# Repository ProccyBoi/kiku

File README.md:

# kiku

kiku is an open-source portable audio player built around an STM32H523 microcontroller. The project combines Bluetooth audio, local microSD playback, FM radio, a colour display, headphone and speaker outputs, battery management, and a custom mechanical enclosure in one hardware/firmware repository.

> **Project status:** this repository is a public engineering snapshot, not a production-approved hardware release. The firmware software gate passes on the checked-in source, but physical product qualification is still in progress. In particular, the Rev-A USB-C/power-path issue and the remaining hardware soak/validation items in [`Firmware/RELEASE_CHECKLIST.md`](Firmware/RELEASE_CHECKLIST.md) must be resolved before treating the design as production-ready. Files under `Production/` are therefore prototype/reference manufacturing outputs, not a production release.

## Features

- Bluetooth A2DP sink with AVRCP transport control and metadata through a Microchip BM83
- WAV and MP3 playback from a 4-bit SDMMC microSD card
- FM tuning, seek and RDS using the Silicon Labs SI4705-D60
- TLV320AIC3104 headphone/codec path and MAX98357A internal-speaker amplifier
- automatic headphone/speaker routing
- 2.0-inch 240 x 320 ST7789 display, rotary encoder and push-button controls
- BQ25895 charging/power-path control and MAX17048 battery state-of-charge monitoring
- FreeRTOS-based STM32H523 firmware with host tests, release/debug builds, watchdogs and diagnostics
- project-owned enclosure CAD, printable parts and mechanical packaging tools

## Hardware

The KiCad project in the repository root is the electrical hardware source of truth. The current board uses:

| Function | Device |
| --- | --- |
| Application MCU | STM32H523VET6 |
| Bluetooth audio | Microchip BM83, A2DP sink |
| Audio codec / headphones | TI TLV320AIC3104 |
| Speaker amplifier | Analog Devices MAX98357A |
| FM receiver | Silicon Labs SI4705-D60 |
| Charger / power path | TI BQ25895 |
| Fuel gauge | Analog Devices MAX17048 |
| Display | HS20HS072RX, ST7789, 240 x 320 |
| Storage | 4-bit SDMMC microSD |

The board is programmed and debugged through **SWD**. On this hardware revision, USB-C D+/D- are used by the BQ25895 input-detection circuitry and are **not routed to STM32 PA11/PA12**, so USB DFU/CDC is not available.

The historical `Walkman - Blobject.*` KiCad/manufacturing filenames are retained in this snapshot to avoid breaking project references and release tooling; the public project name is **kiku**.

## Firmware

Firmware is under [`Firmware/`](Firmware/README.md). It implements Bluetooth, local-file and FM source handling; audio routing; display and controls; battery/charger monitoring; persistent settings; watchdog/fault handling; and bring-up diagnostics.

Initialise the pinned submodules and run the host/build checks from the repository root:

```text
git submodule update --init --recursive
python Firmware/tools/test_host.py
python Firmware/tools/build.py --clean
```

For a software release candidate, run:

```text
python Firmware/tools/release_check.py --require-clean
```

The firmware build outputs `kiku.elf`, `kiku.bin`, `kiku.hex` and `kiku.map` under `Firmware/build/`. See [`Firmware/README.md`](Firmware/README.md) for the BM83 configuration contract, programming steps, controls and bring-up details.

## Mechanical design

[`Mechanical/`](Mechanical/README.md) contains the enclosure source, public STEP/STL outputs, review material and packaging scripts.

The project intentionally does **not** redistribute component 3D models whose upstream redistribution terms are unclear, nor generated populated/reference assemblies that embed those models. Public mechanical packages use project-owned geometry and recorded QA metadata. Exact component-level fit checking remains a local workflow after obtaining the required manufacturer/KiCad models under their original terms.

See [`Mechanical/REFERENCE_GEOMETRY.md`](Mechanical/REFERENCE_GEOMETRY.md) for the complete provenance and reproducibility workflow.

## Repository layout

```text
Firmware/                       STM32 firmware, tests and build/release tooling
Mechanical/                     enclosure CAD, exports, QA and packaging tools
Production/                     prototype/reference PCB manufacturing outputs
3dmodels/README.md              policy for locally obtained component models
Walkman - Blobject.kicad_*      KiCad project sources
Print.pdf                       generated PCB print output
Print Schematic.pdf             generated schematic print output
.github/workflows/firmware.yml  firmware CI
```

## Public-source scope

This repository publishes project-authored hardware, firmware and mechanical sources while deliberately excluding material that should remain with its upstream publisher. Excluded material includes third-party BM83 firmware/configuration tools and command-set documents, generated radio images, cached supplier pages, vendor datasheet copies, provenance-unclear component 3D models, and fit-check assemblies that serialise those models.

Third-party source code that is present in the tree or pulled as a submodule remains under its own upstream copyright and licence notices. The project licence does not replace those terms.

## Validation

The public snapshot is checked with:

- native firmware regression tests plus clean release/debug ARM builds;
- `Firmware/tools/release_check.py --require-clean`;
- stripped-checkout P0/P1 mechanical package builds that exclude third-party reference geometry;
- Git history, integrity, privacy and credential scans before publication.

Passing these source/software checks does not replace the physical hardware, RF, charging, mechanical, regulatory or long-duration soak tests listed in [`Firmware/RELEASE_CHECKLIST.md`](Firmware/RELEASE_CHECKLIST.md).

## Licence

kiku is a mixed-licence project:

- project-authored hardware, electronics and mechanical design material is licensed under **CERN-OHL-P-2.0**;
- project-authored firmware, tools, scripts and CI code is licensed under the **MIT License**;
- files or portions carrying their own third-party copyright/licence notices remain under those upstream terms.

The exact scope map and full licence texts are in [`LICENSE`](LICENSE) and [`LICENSES/`](LICENSES/).

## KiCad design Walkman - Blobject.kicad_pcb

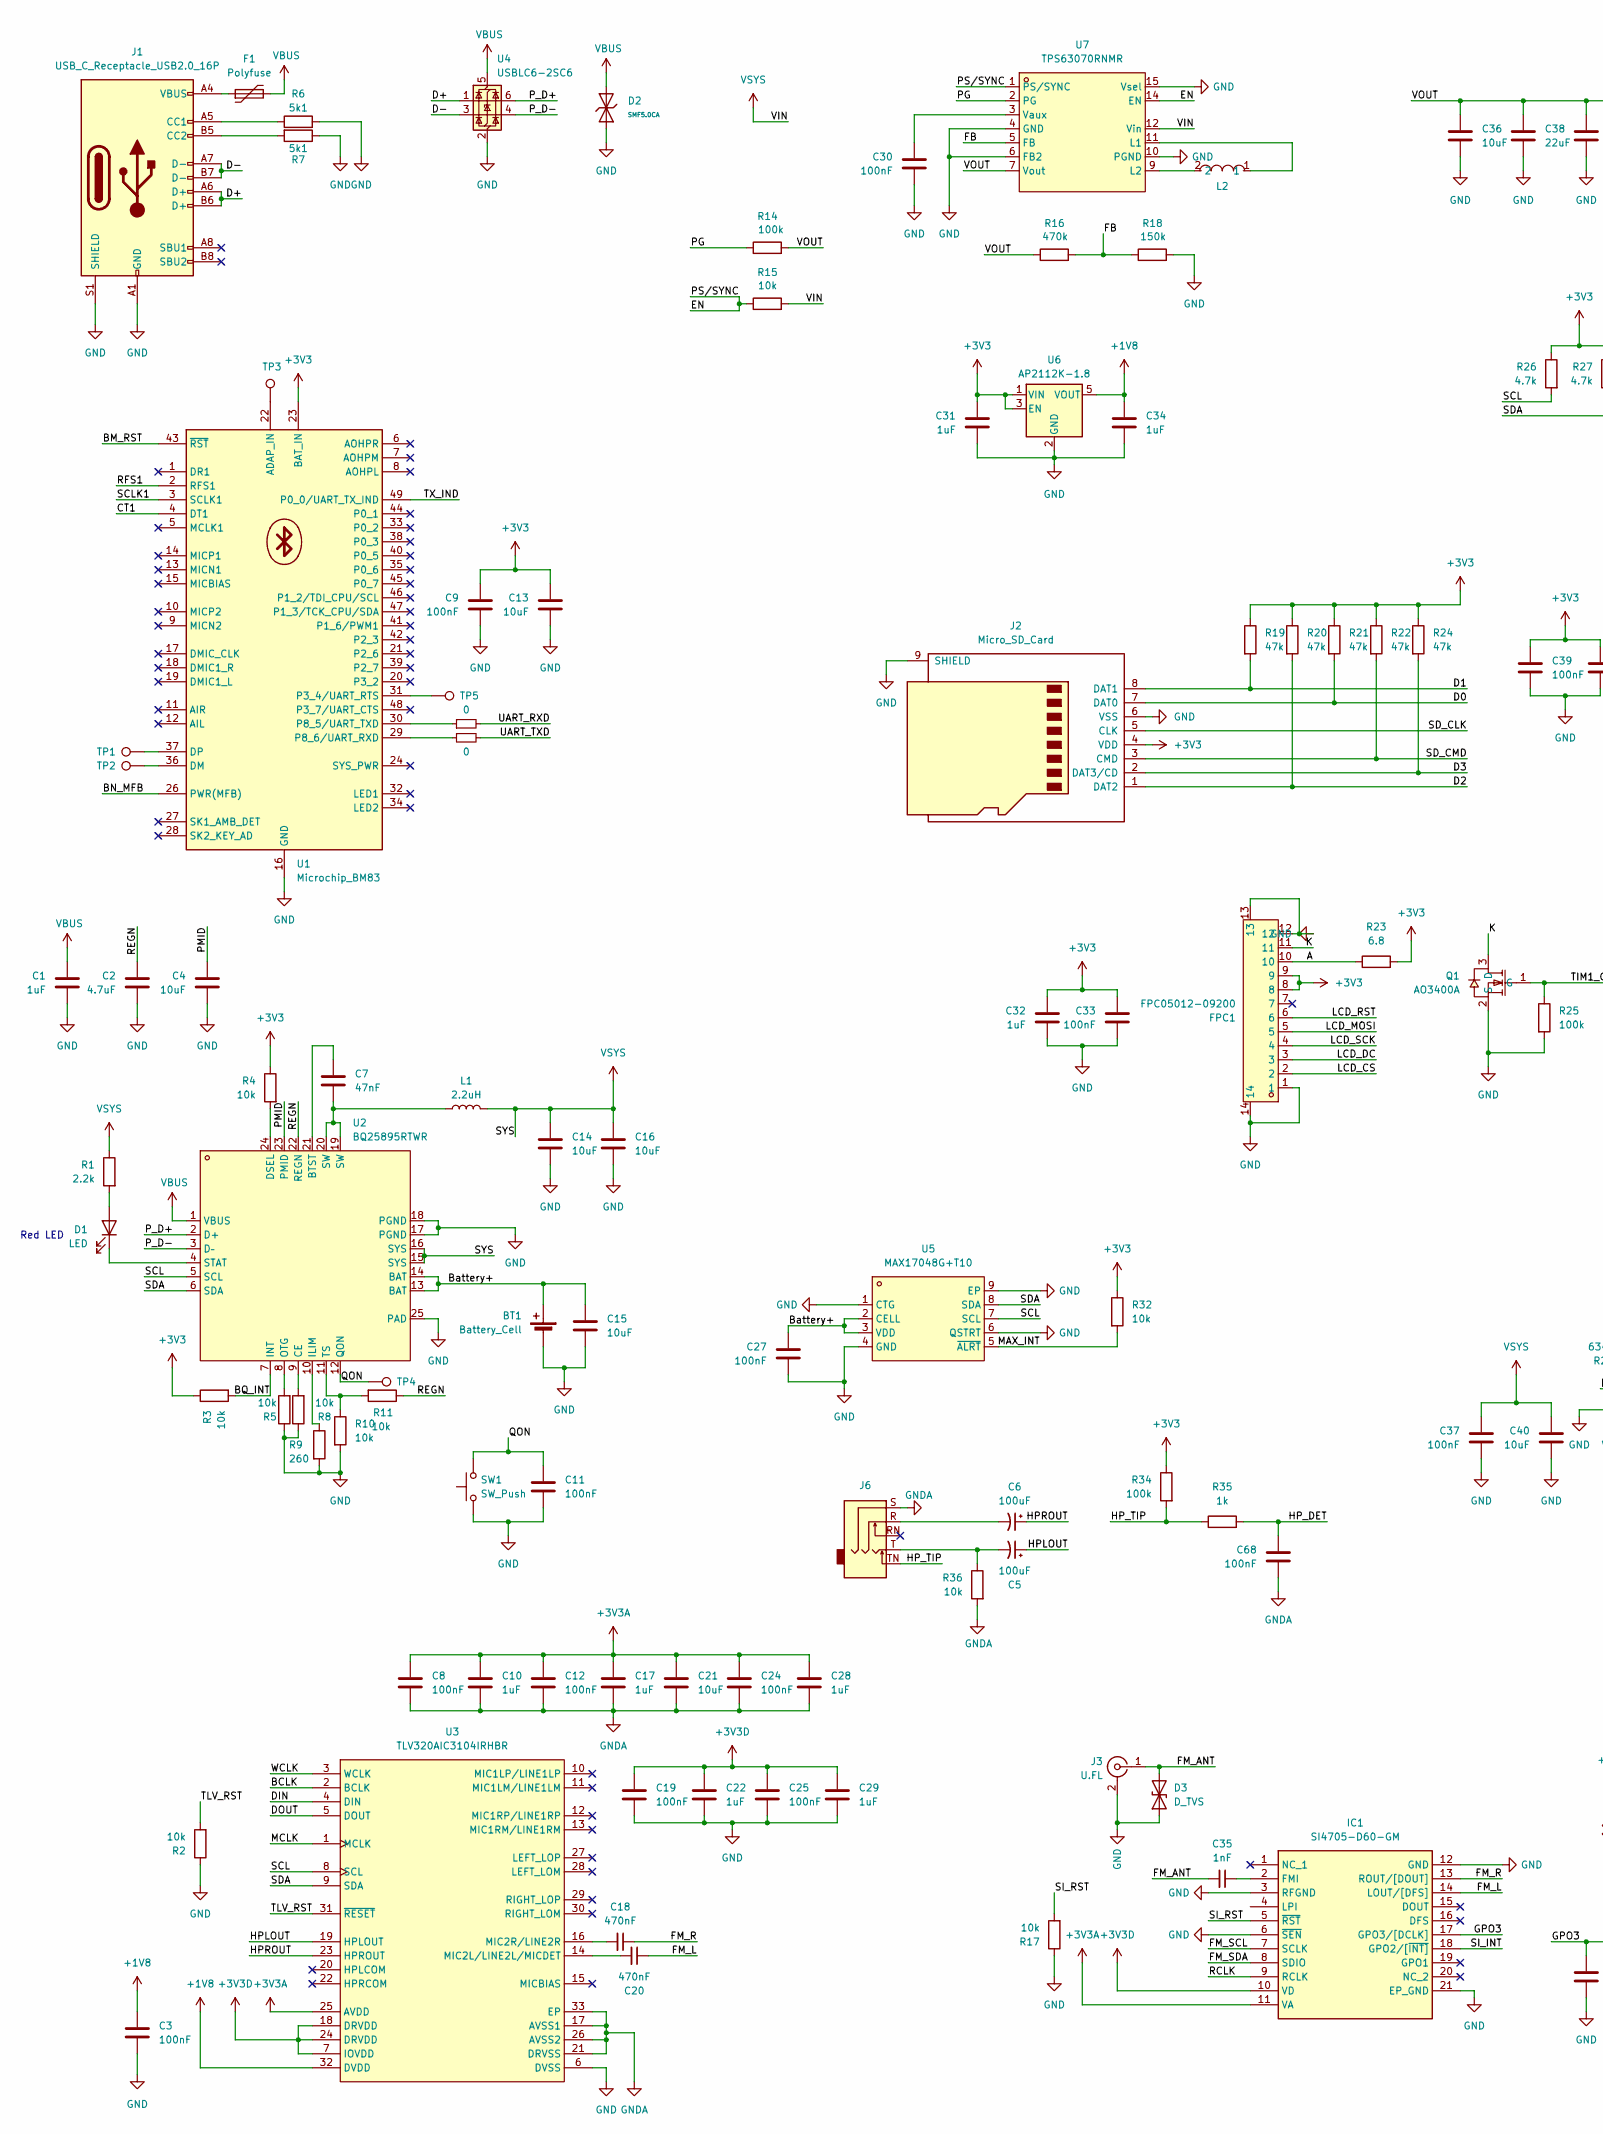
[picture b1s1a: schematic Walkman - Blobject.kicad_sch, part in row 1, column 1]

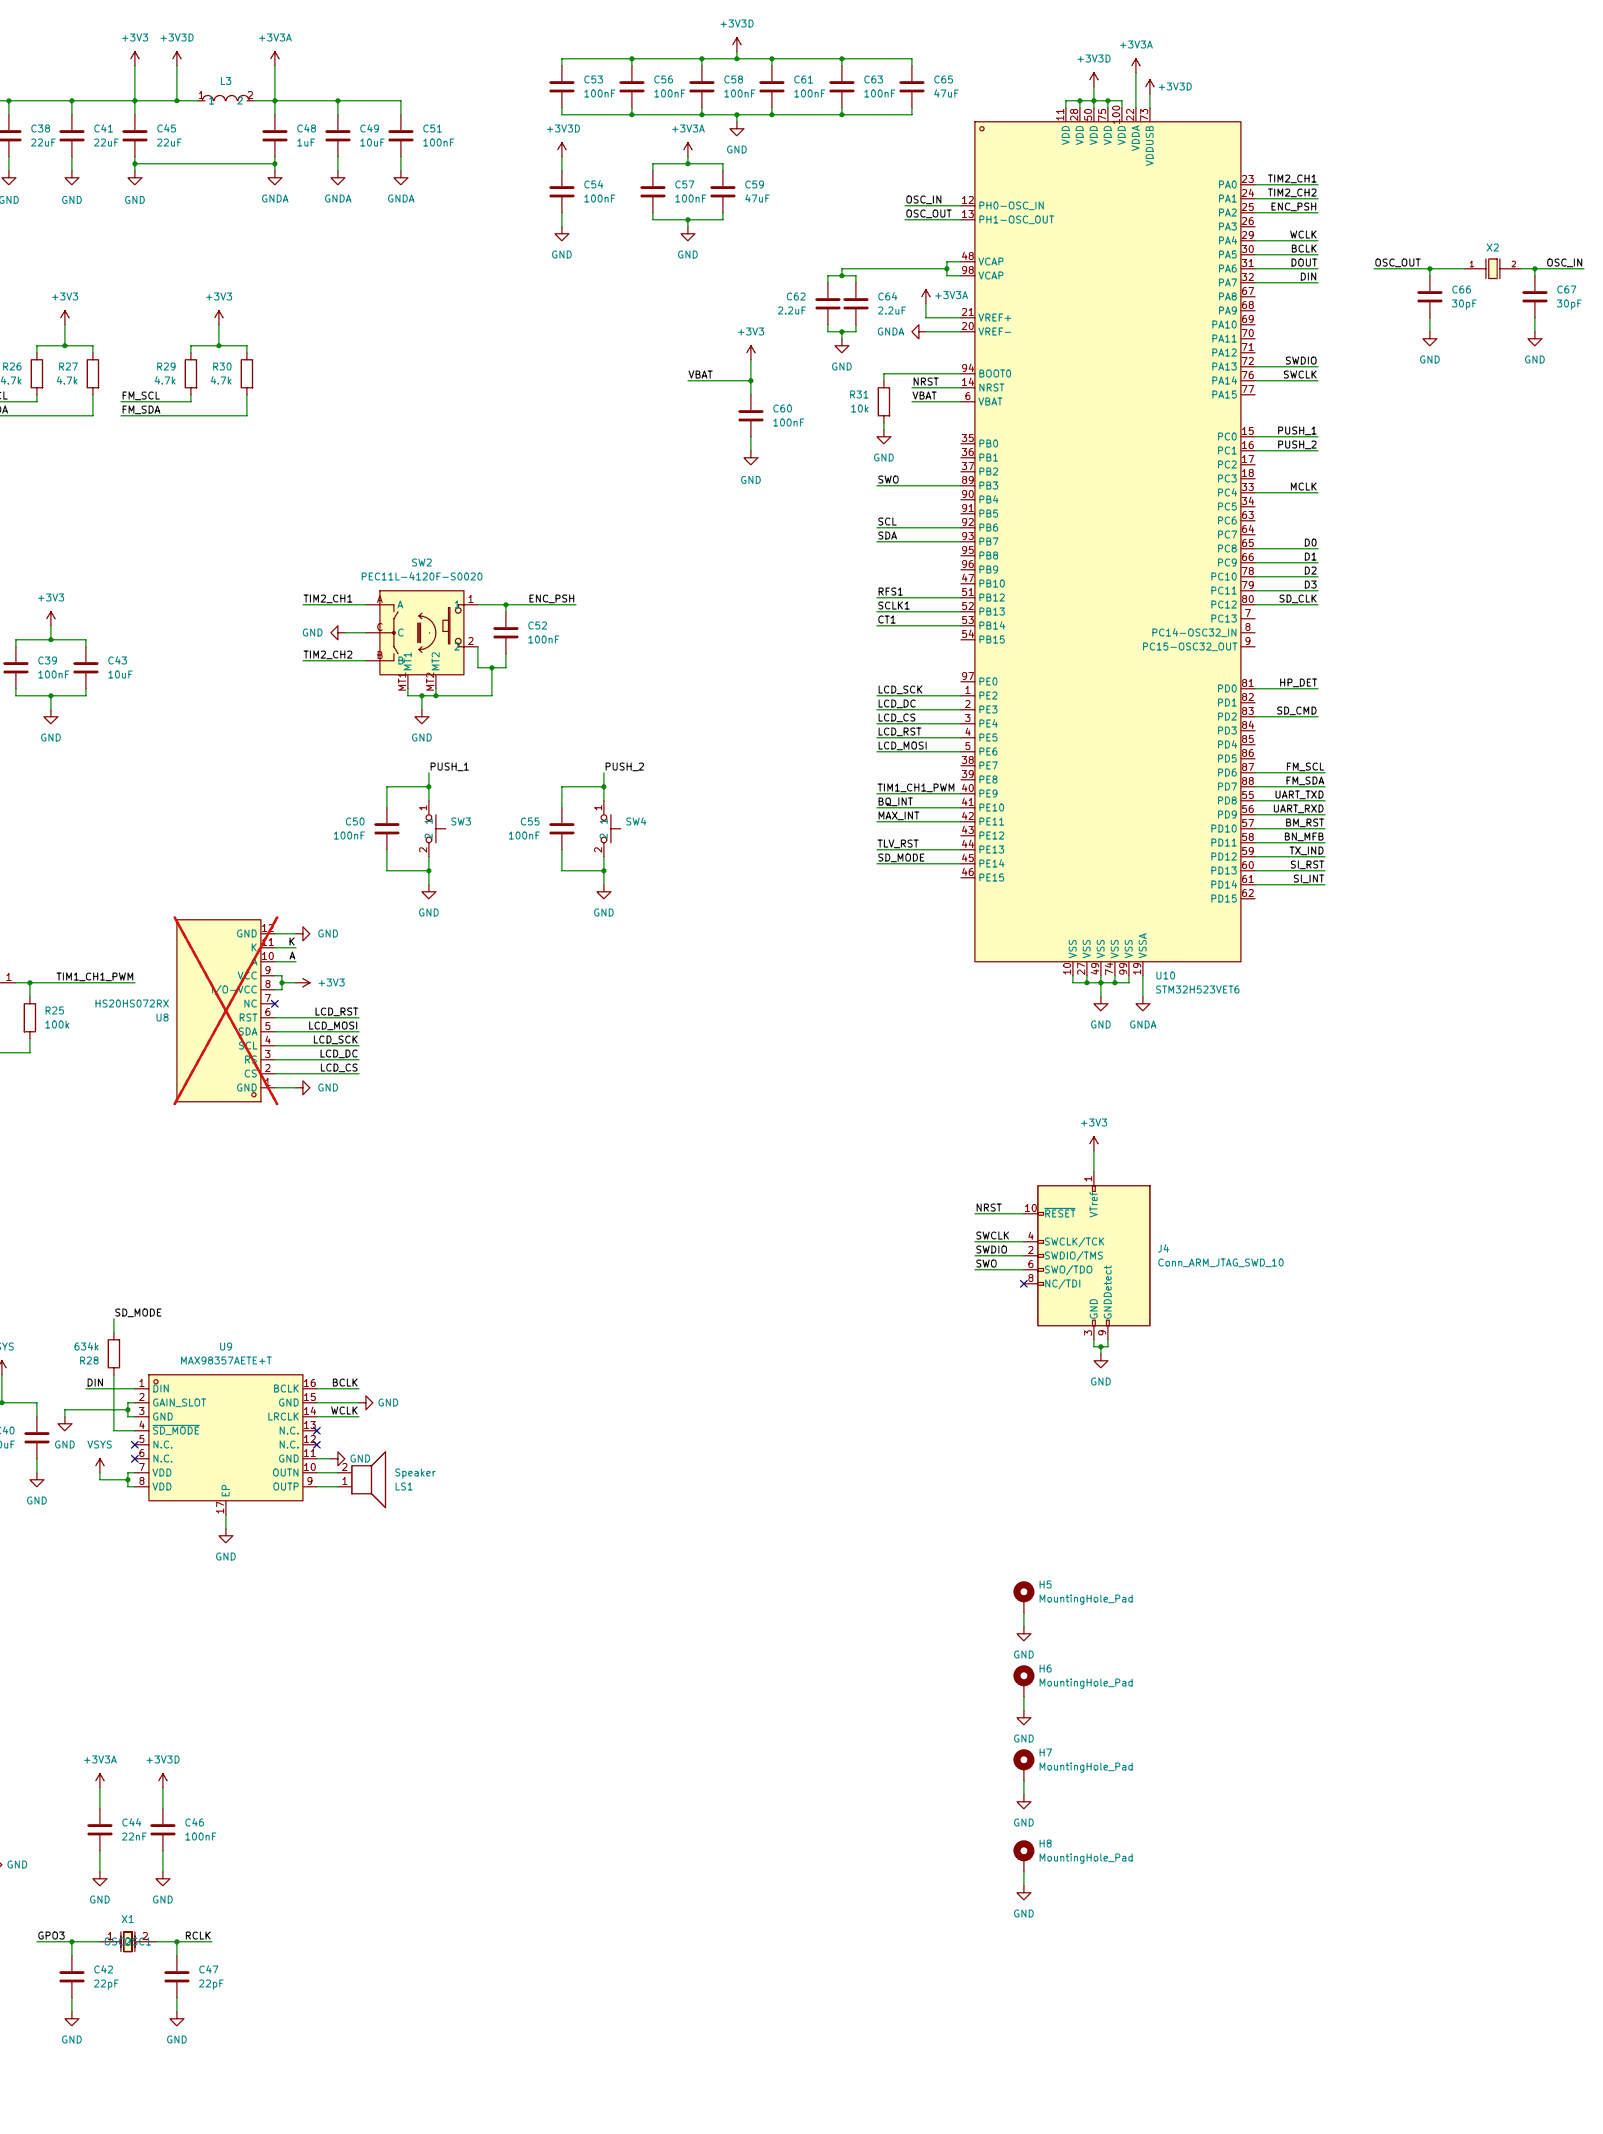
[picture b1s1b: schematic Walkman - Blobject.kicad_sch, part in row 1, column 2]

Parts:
BT1: Battery_Cell; JST_PH_B2B-PH-K_1x02_P2.00mm_Vertical
C1, C10, C17, C22, C28, C29, C31, C32, C34, C48: 1uF; C_0603_1608Metric
C2: 4.7uF; C_0603_1608Metric
C3, C8, C9, C11, C12, C19, C24, C25, C27, C30, C33, C37, C39, C46, C50, C51, C52, C53, C54, C55, C56, C57, C58, C60, C61, C63, C68: 100nF; C_0603_1608Metric
C4, C13, C14, C15, C16, C21, C36, C40, C43, C49: 10uF; C_0603_1608Metric
C5, C6: 100uF; CP_Elec_5x5.4
C7: 47nF; C_0603_1608Metric
C18, C20: 470nF; C_0603_1608Metric
C35: 1nF; C_0201_0603Metric
C38, C41, C45: 22uF; C_0603_1608Metric
C42, C47: 22pF; C_0603_1608Metric
C44: 22nF; C_0603_1608Metric
C59, C65: 47uF; C_0603_1608Metric
C62, C64: 2.2uF; C_0603_1608Metric
C66, C67: 30pF; C_0603_1608Metric
D1: LED; LED_0603_1608Metric
D2: SMF5.0CA; D_SOD-123FL; Part SMF5.0CA; LCSC C19077498
D3: D_TVS; D_0201_0603Metric; LCSC C672369
F1: Polyfuse; Fuse_1206_3216Metric; LCSC C883127
FPC1: FPC05012-09200; FPC-SMD_FPC05012-09200; MPN FPC05012-09200; LCSC Part C479750
H5, H6, H7, H8: MountingHole_Pad; MountingHole_2.2mm_M2_Pad_Via
IC1: SI4705-D60-GM; SI4705D60GM; Manufacturer_Part_Number SI4705-D60-GM; Mouser Part Number N/A
J1: USB_C_Receptacle_USB2.0_16P; USB_C_Receptacle_HRO_TYPE-C-31-M-12; LCSC C2765186
J2: Micro_SD_Card; microSD_HC_Hirose_DM3AT-SF-PEJM5
J3: U.FL; IPEX-SMD_BWIPX-1-001E; LCSC C5137195
J4: Conn_ARM_JTAG_SWD_10; PinHeader_2x05_P1.27mm_Vertical
J6: AudioJack3_SwitchTR; Jack_3.5mm_CUI_SJ1-3525N_Horizontal
L1: 2.2uH; IND-SMD_L5.0-W5.0_SWPA5040S
L2: XFL4020-152MEC; IND-SMD_L4.0-W4.0-A; MPN XFL4020-152MEC; LCSC Part C3033018
L3: MPZ2012S601AT000; L0805; MPN MPZ2012S601AT000; LCSC Part C21519
LS1: Speaker; Molex_PicoBlade_53398-0271_1x02-1MP_P1.25mm_Vertical
Q1: AO3400A; SOT-23-3_L2.9-W1.3-P1.90-LS2.4-BR; MPN AO3400A; LCSC Part C20917
R1: 2.2k; R_0603_1608Metric
R2, R3, R4, R5, R8, R10, R11, R15, R17, R31, R32, R36: 10k; R_0603_1608Metric
R6, R7: 5k1; R_0603_1608Metric; LCSC C27834
R9: 260; R_0603_1608Metric
R12, R13: 0; R_0603_1608Metric
R14, R25, R34: 100k; R_0603_1608Metric
R16: 470k; R_0603_1608Metric
R18: 150k; R_0603_1608Metric
R19, R20, R21, R22, R24: 47k; R_0603_1608Metric; LCSC C17673
R23: 6.8; R_0603_1608Metric; LCSC C17673
R26, R27, R29, R30: 4.7k; R_0603_1608Metric
R28: 634k; R_0603_1608Metric
R35: 1k; R_0603_1608Metric; LCSC C17673
SW1: SW_Push; SW-SMD_L3.9-W3.0-P4.45
SW2: PEC11L-4120F-S0020; SW-TH_PEC11R-4XXXF-SXXXX; MPN PEC11L-4120F-S0020; LCSC Part C20882995
SW3, SW4: SW_PUSH_12x12x12mm_4Pin_SMD; MPN 12x12x12mm 4-pin tactile pushbutton
TP1, TP2, TP3, TP4, TP5: TestPoint; TestPoint_Pad_D1.0mm
U1: Microchip_BM83
U2: BQ25895RTWR; QFN-24_L4.0-W4.0-P0.50-TL-EP2.7; MPN BQ25895RTWR; LCSC Part C80200
U3: TLV320AIC3104IRHBR; HVQFN-32_L5.0-W5.0-P0.50-TL-EP; MPN TLV320AIC3104IRHBR; LCSC Part C181753
U4: USBLC6-2SC6; SOT-23-6
U5: MAX17048G+T10; TDFN-8_L2.0-W2.0-P0.50-BL-EP1.2; MPN MAX17048G+T10; LCSC Part C2682616
U6: AP2112K-1.8; SOT-23-5
U7: TPS63070RNMR; VQFN-15_L3.0-W2.5-P0.50-BL; MPN TPS63070RNMR; LCSC Part C109322
U8: HS20HS072RX; OLED-SMD_HS20HS072RX; MPN HS20HS072RX; LCSC Part C5329582; not fitted
U9: MAX98357AETE+T; TQFN-16_L3.0-W3.0-P0.50-BL-EP1.5; MPN MAX98357AETE+T; LCSC Part C910544
U10: STM32H523VET6; LQFP-100_L14.0-W14.0-P0.50-LS16.0-BL; MPN STM32H523VET6; LCSC Part C27338462
X1: ABS07-32.768KHZ-T; OSC-SMD_2P-L3.2-W1.5; MPN ABS07-32.768KHZ-T; LCSC Part C130253
X2: X50328MSB2GI; CRYSTAL-SMD_L5.0-W3.2; Frequency Tolerance ±10ppm; Part X50328MSB2GI; LCSC C115962

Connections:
+1V8: C3.2, C34.2, U3.32 (DVDD), U6.5 (VOUT)
+3V3: C9.1, C13.1, C19.1, C22.1, C25.1, C29.1, C31.2, C32.1, C33.1, C36.1, C38.1, C39.1, C41.1, C43.1, C45.1, C46.1, C53.1, C54.1, C56.1, C58.1, C60.1, C61.1, C63.1, C65.1, FPC1.8, FPC1.9, IC1.10 (VD), J2.4 (VDD), J4.1 (VTref), L3.1, R3.1, R4.1, R14.2, R16.1, R19.1, R20.1, R21.1, R22.1, R23.2, R24.1, R26.1, R27.1, R29.1, R30.1, R32.1, R34.1, U1.23 (BAT_IN), U3.7 (IOVDD), U3.18 (DRVDD), U3.24 (DRVDD), U6.1 (VIN), U6.3 (EN), U7.7 (Vout), U8.8 (I/O-VCC), U8.9 (VCC), U10.6 (VBAT), U10.11 (VDD), U10.28 (VDD), U10.50 (VDD), U10.73 (VDDUSB), U10.75 (VDD), U10.100 (VDD)
+3V3A: C8.1, C10.1, C12.1, C17.1, C21.1, C24.1, C28.1, C44.1, C48.1, C49.1, C51.1, C57.1, C59.1, IC1.11 (VA), L3.2, U3.25 (AVDD), U10.21 (VREF+), U10.22 (VDDA)
/A: FPC1.10, R23.1, U8.10 (A)
/BCLK: U3.2 (BCLK), U9.16 (BCLK), U10.30 (PA5)
/BM_RST: U1.43 (~RST), U10.57 (PD10)
/BN_MFB: U1.26 (PWR(MFB)), U10.58 (PD11)
/BQ_INT: R3.2, U2.7 (INT), U10.41 (PE10)
/Battery+: BT1.1 (+), C15.1, C27.2, U2.13 (BAT), U2.14 (BAT), U5.2 (CELL), U5.3 (VDD)
/CT1: U1.4 (DT1), U10.53 (PB14)
/D0: J2.7 (DAT0), R21.2, U10.65 (PC8)
/D1: J2.8 (DAT1), R19.2, U10.66 (PC9)
/D2: J2.1 (DAT2), R20.2, U10.78 (PC10)
/D3: J2.2 (DAT3/CD), R24.2, U10.79 (PC11)
/D+: J1.A6 (D+), J1.B6 (D+), U4.1 (I/O1)
/D-: J1.A7 (D-), J1.B7 (D-), U4.3 (I/O2)
/DIN: U3.4 (DIN), U9.1 (DIN), U10.32 (PA7)
/DOUT: U3.5 (DOUT), U10.31 (PA6)
/EN: R15.1, U7.1 (PS/SYNC), U7.14 (EN)
/ENC_PSH: C52.1, SW2.1, U10.25 (PA2)
/FB: R16.2, R18.1, U7.5 (FB)
/FM_ANT: C35.2, D3.2 (A2), J3.1 (In)
/FM_L: C20.1, IC1.14 (LOUT/[DFS])
/FM_R: C18.1, IC1.13 (ROUT/[DOUT])
/FM_SCL: IC1.7 (SCLK), R29.2, U10.87 (PD6)
/FM_SDA: IC1.8 (SDIO), R30.2, U10.88 (PD7)
/GPO3: C42.1, IC1.17 (GPO3/[DCLK]), X1.1 (OSC1)
/HPLOUT: C5.1, U3.19 (HPLOUT)
/HPROUT: C6.1, U3.23 (HPROUT)
/HP_DET: C68.1, R35.2, U10.81 (PD0)
/HP_TIP: J6.TN, R34.2, R35.1
/K: FPC1.11, Q1.3 (D), U8.11 (K)
/LCD_CS: FPC1.2, U8.2 (CS), U10.3 (PE4)
/LCD_DC: FPC1.3, U8.3 (RS), U10.2 (PE3)
/LCD_MOSI: FPC1.5, U8.5 (SDA), U10.5 (PE6)
/LCD_RST: FPC1.6, U8.6 (RST), U10.4 (PE5)
/LCD_SCK: FPC1.4, U8.4 (SCL), U10.1 (PE2)
/MAX_INT: R32.2, U5.5 (~ALRT), U10.42 (PE11)
/MCLK: U3.1 (MCLK), U10.33 (PC4)
/NRST: J4.10 (~RESET), U10.14 (NRST)
/OSC_IN: C67.1, U10.12 (PH0-OSC_IN), X2.2
/OSC_OUT: C66.1, U10.13 (PH1-OSC_OUT), X2.1
/PG: R14.1, U7.2 (PG)
/PMID: C4.1, U2.23 (PMID)
/PUSH_1: C50.1, SW3.1, U10.15 (PC0)
/PUSH_2: C55.1, SW4.1, U10.16 (PC1)
/P_D+: U2.2 (D+), U4.6 (I/O1)
/P_D-: U2.3 (D–), U4.4 (I/O2)
/QON: C11.1, SW1.2, TP4.1, U2.12 (QON)
/RCLK: C47.1, IC1.9 (RCLK), X1.2 (OSC2)
/REGN: C2.1, R11.1, U2.22 (REGN)
/RFS1: U1.2 (RFS1), U10.51 (PB12)
/SCL: R26.2, U2.5 (SCL), U3.8 (SCL), U5.7 (SCL), U10.92 (PB6)
/SCLK1: U1.3 (SCLK1), U10.52 (PB13)
/SDA: R27.2, U2.6 (SDA), U3.9 (SDA), U5.8 (SDA), U10.93 (PB7)
/SD_CLK: J2.5 (CLK), U10.80 (PC12)
/SD_CMD: J2.3 (CMD), R22.2, U10.83 (PD2)
/SD_MODE: R28.2, U10.45 (PE14)
/SI_INT: IC1.18 (GPO2/[~INT]), U10.61 (PD14)
/SI_RST: IC1.5 (~RST), R17.2, U10.60 (PD13)
/SWCLK: J4.4 (SWCLK/TCK), U10.76 (PA14)
/SWDIO: J4.2 (SWDIO/TMS), U10.72 (PA13)
/SWO: J4.6 (SWO/TDO), U10.89 (PB3)
/TIM1_CH1_PWM: Q1.1 (G), R25.1, U10.40 (PE9)
/TIM2_CH1: SW2.A, U10.23 (PA0)
/TIM2_CH2: SW2.B, U10.24 (PA1)
/TLV_RST: R2.2, U3.31 (~RESET), U10.44 (PE13)
/TX_IND: U1.49 (P0_0/UART_TX_IND), U10.59 (PD12)
/UART_RXD: R12.2, U10.56 (PD9)
/UART_TXD: R13.2, U10.55 (PD8)
/WCLK: U3.3 (WCLK), U9.14 (LRCLK), U10.29 (PA4)
GND: BT1.2 (-), C1.2, C2.2, C3.1, C4.2, C8.2, C9.2, C10.2, C11.2, C12.2, C13.2, C14.2, C15.2, C16.2, C17.2, C19.2, C21.2, C22.2, C24.2, C25.2, C27.1, C28.2, C29.2, C30.1, C31.1, C32.2, C33.2, C34.1, C36.2, C37.2, C38.2, C39.2, C40.2, C41.2, C42.2, C43.2, C44.2, C45.2, C46.2, C47.2, C48.2, C49.2, C50.2, C51.2, C52.2, C53.2, C54.2, C55.2, C56.2, C57.2, C58.2, C59.2, C60.2, C61.2, C62.2, C63.2, C64.2, C65.2, C66.2, C67.2, C68.2, D2.1, D3.1 (A1), FPC1.1, FPC1.12, FPC1.13, FPC1.14, H5.1, H6.1, H7.1, H8.1, IC1.3 (RFGND), IC1.6 (~SEN), IC1.12 (GND), IC1.21 (EP_GND), J1.A1 (GND), J1.A12 (GND), J1.B1 (GND), J1.B12 (GND), J1.S1 (SHIELD), J2.6 (VSS), J2.9 (SHIELD), J3.2 (Ext), J4.3 (GND), J4.5 (GND), J4.9 (GNDDetect), J6.S, Q1.2 (S), R2.1, R5.1, R6.2, R7.1, R8.1, R9.2, R10.2, R17.1, R18.2, R25.2, R31.2, R36.2, SW1.1, SW2.2, SW2.C, SW2.MT1, SW2.MT2, SW3.2, SW4.2, U1.16 (GND), U1.50 (GND), U1.56 (GND), U1.57 (GND), U2.17 (PGND), U2.18 (PGND), U2.25 (PAD), U3.6 (DVSS), U3.17 (AVSS1), U3.21 (DRVSS), U3.26 (AVSS2), U3.33 (EP), U4.2 (GND), U5.1 (CTG), U5.4 (GND), U5.6 (QSTRT), U5.9 (EP), U6.2 (GND), U7.4 (GND), U7.6 (FB2), U7.10 (PGND), U7.15 (Vsel), U8.1 (GND), U8.12 (GND), U9.2 (GAIN_SLOT), U9.3 (GND), U9.11 (GND), U9.15 (GND), U9.17 (EP), U10.10 (VSS), U10.19 (VSSA), U10.20 (VREF-), U10.27 (VSS), U10.49 (VSS), U10.74 (VSS), U10.99 (VSS)
unnamed: C5.2, J6.T, R36.1
unnamed: C6.2, J6.R
unnamed: C7.2, L1.1, U2.19 (SW), U2.20 (SW)
unnamed: C62.1, C64.1, U10.48 (VCAP), U10.98 (VCAP)
unnamed: D1.2 (A), R1.2
unnamed: D1.1 (K), U2.4 (STAT)
unnamed: F1.1, J1.A4 (VBUS), J1.A9 (VBUS), J1.B4 (VBUS), J1.B9 (VBUS)
unnamed: C35.1, IC1.2 (FMI)
unnamed: J1.A5 (CC1), R6.1
unnamed: J1.B5 (CC2), R7.2
unnamed: TP3.1, U1.22 (ADAP_IN)
unnamed: TP2.1, U1.36 (DM)
unnamed: TP1.1, U1.37 (DP)
unnamed: TP5.1, U1.31 (P3_4/UART_RTS)
unnamed: R12.1, U1.30 (P8_5/UART_TXD)
unnamed: R13.1, U1.29 (P8_6/UART_RXD)
unnamed: C7.1, U2.21 (BTST)
unnamed: R8.2, U2.9 (CE)
unnamed: R4.2, U2.24 (DSEL)
unnamed: R9.1, U2.10 (ILIM)
unnamed: R5.2, U2.8 (OTG)
unnamed: R10.1, R11.2, U2.11 (TS)
unnamed: C20.2, U3.14 (MIC2L/LINE2L/MICDET)
unnamed: C18.2, U3.16 (MIC2R/LINE2R)
unnamed: L2.1, U7.11 (L1)
unnamed: L2.2, U7.9 (L2)
unnamed: C30.2, U7.3 (Vaux)
unnamed: LS1.2, U9.10 (OUTN)
unnamed: LS1.1, U9.9 (OUTP)
unnamed: R28.1, U9.4 (~SD_MODE)
unnamed: R31.1, U10.94 (BOOT0)
VBUS: C1.1, D2.2, F1.2, U2.1 (VBUS), U4.5 (VBUS)
VSYS: C14.1, C16.1, C37.1, C40.1, L1.2, R1.1, R15.2, U2.15 (SYS), U2.16 (SYS), U7.12 (Vin), U9.7 (VDD), U9.8 (VDD)

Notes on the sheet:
Red LED

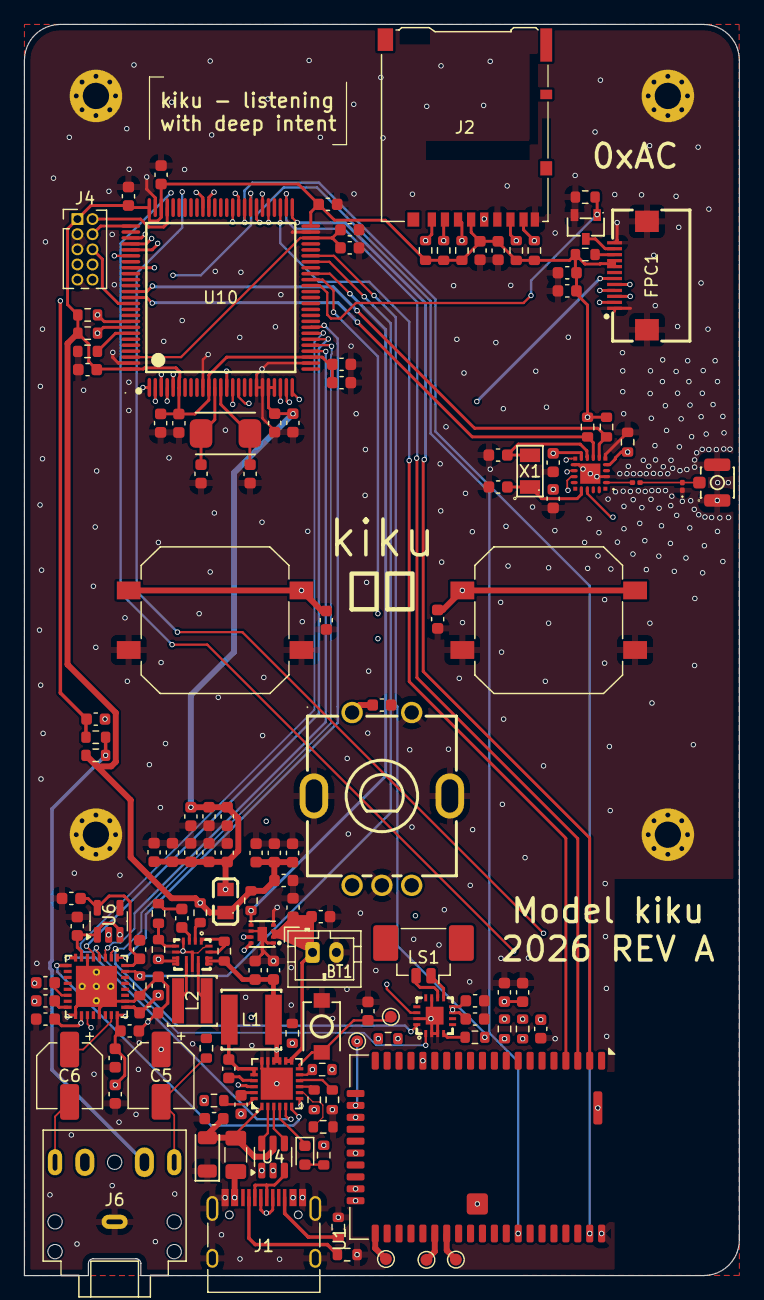
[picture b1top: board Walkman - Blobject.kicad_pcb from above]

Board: 4 copper layers, 60.0 x 105.0 mm, 142 parts (0 on the bottom side), 105 nets.

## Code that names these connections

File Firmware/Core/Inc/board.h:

#ifndef KIKU_BOARD_H
#define KIKU_BOARD_H

#include "stm32h5xx_hal.h"

#ifdef __cplusplus
extern "C" {
#endif

/* Verified MCU clock source. */
#define BOARD_HSE_HZ                    8000000UL
#define BOARD_SYSCLK_HZ               160000000UL
#define BOARD_AUDIO_SAMPLE_RATE_HZ        48000UL

/* LCD: HS20HS072RX/ST7789 through FPC1. */
#define LCD_SCK_Pin                    GPIO_PIN_2
#define LCD_SCK_GPIO_Port              GPIOE
#define LCD_DC_Pin                     GPIO_PIN_3
#define LCD_DC_GPIO_Port               GPIOE
#define LCD_CS_Pin                     GPIO_PIN_4
#define LCD_CS_GPIO_Port               GPIOE
#define LCD_RST_Pin                    GPIO_PIN_5
#define LCD_RST_GPIO_Port              GPIOE
#define LCD_MOSI_Pin                   GPIO_PIN_6
#define LCD_MOSI_GPIO_Port             GPIOE

/* User controls. PUSH_1 and HP_DET both occupy EXTI line 0, so these
 * application-facing inputs are intentionally polled rather than EXTI-driven. */
#define PUSH_1_Pin                     GPIO_PIN_0
#define PUSH_1_GPIO_Port               GPIOC
#define PUSH_2_Pin                     GPIO_PIN_1
#define PUSH_2_GPIO_Port               GPIOC
#define ENC_A_Pin                      GPIO_PIN_0
#define ENC_A_GPIO_Port                GPIOA
#define ENC_B_Pin                      GPIO_PIN_1
#define ENC_B_GPIO_Port                GPIOA
#define ENC_PUSH_Pin                   GPIO_PIN_2
#define ENC_PUSH_GPIO_Port             GPIOA
#define HP_DET_Pin                     GPIO_PIN_0
#define HP_DET_GPIO_Port               GPIOD

/* I2S1: MCU master to TLV320AIC3104 and MAX98357A, with codec return data. */
#define AUDIO_WCLK_Pin                 GPIO_PIN_4
#define AUDIO_WCLK_GPIO_Port           GPIOA
#define AUDIO_BCLK_Pin                 GPIO_PIN_5
#define AUDIO_BCLK_GPIO_Port           GPIOA
#define AUDIO_DOUT_Pin                 GPIO_PIN_6
#define AUDIO_DOUT_GPIO_Port           GPIOA
#define AUDIO_DIN_Pin                  GPIO_PIN_7
#define AUDIO_DIN_GPIO_Port            GPIOA
#define AUDIO_MCLK_Pin                 GPIO_PIN_4
#define AUDIO_MCLK_GPIO_Port           GPIOC

/* Backlight and audio control. */
#define LCD_BL_PWM_Pin                 GPIO_PIN_9
#define LCD_BL_PWM_GPIO_Port           GPIOE
#define BQ_INT_Pin                     GPIO_PIN_10
#define BQ_INT_GPIO_Port               GPIOE
#define MAX_INT_Pin                    GPIO_PIN_11
#define MAX_INT_GPIO_Port              GPIOE
#define TLV_RST_Pin                    GPIO_PIN_13
#define TLV_RST_GPIO_Port              GPIOE
#define AMP_SD_MODE_Pin                GPIO_PIN_14
#define AMP_SD_MODE_GPIO_Port          GPIOE

/* BM83 digital audio and host interface. KiCad net /CT1 is BM83 DT1. */
#define BM83_RFS_Pin                   GPIO_PIN_12
#define BM83_RFS_GPIO_Port             GPIOB
#define BM83_SCLK_Pin                  GPIO_PIN_13
#define BM83_SCLK_GPIO_Port            GPIOB
#define BM83_DT_Pin                    GPIO_PIN_14
#define BM83_DT_GPIO_Port              GPIOB
#define BM83_UART_TX_Pin               GPIO_PIN_8
#define BM83_UART_TX_GPIO_Port         GPIOD
#define BM83_UART_RX_Pin               GPIO_PIN_9
#define BM83_UART_RX_GPIO_Port         GPIOD
#define BM83_RST_Pin                   GPIO_PIN_10
#define BM83_RST_GPIO_Port             GPIOD
#define BM83_MFB_Pin                   GPIO_PIN_11
#define BM83_MFB_GPIO_Port             GPIOD
#define BM83_TX_IND_Pin                GPIO_PIN_12
#define BM83_TX_IND_GPIO_Port          GPIOD

/* SI4705 FM tuner. */
#define SI4705_RST_Pin                 GPIO_PIN_13
#define SI4705_RST_GPIO_Port           GPIOD
#define SI4705_INT_Pin                 GPIO_PIN_14
#define SI4705_INT_GPIO_Port           GPIOD
#define FM_SCL_Pin                     GPIO_PIN_6
#define FM_SCL_GPIO_Port               GPIOD
#define FM_SDA_Pin                     GPIO_PIN_7
#define FM_SDA_GPIO_Port               GPIOD

/* microSD, native 4-bit SDMMC1. */
#define SD_D0_Pin                      GPIO_PIN_8
#define SD_D0_GPIO_Port                GPIOC
#define SD_D1_Pin                      GPIO_PIN_9
#define SD_D1_GPIO_Port                GPIOC
#define SD_D2_Pin                      GPIO_PIN_10
#define SD_D2_GPIO_Port                GPIOC
#define SD_D3_Pin                      GPIO_PIN_11
#define SD_D3_GPIO_Port                GPIOC
#define SD_CLK_Pin                     GPIO_PIN_12
#define SD_CLK_GPIO_Port               GPIOC
#define SD_CMD_Pin                     GPIO_PIN_2
#define SD_CMD_GPIO_Port               GPIOD

/* Shared I2C1 bus: BQ25895 + TLV320AIC3104 + MAX17048. */
#define SYS_I2C_SCL_Pin                GPIO_PIN_6
#define SYS_I2C_SCL_GPIO_Port          GPIOB
#define SYS_I2C_SDA_Pin                GPIO_PIN_7
#define SYS_I2C_SDA_GPIO_Port          GPIOB

extern I2C_HandleTypeDef hi2c1;
extern I2C_HandleTypeDef hi2c3;
extern SPI_HandleTypeDef hspi4;
extern I2S_HandleTypeDef hi2s1;
extern I2S_HandleTypeDef hi2s2;
extern UART_HandleTypeDef huart3;
extern SD_HandleTypeDef hsd1;
extern TIM_HandleTypeDef htim1;
extern TIM_HandleTypeDef htim2;
extern IWDG_HandleTypeDef hiwdg;

extern DMA_HandleTypeDef hdma_spi1_rx;
extern DMA_HandleTypeDef hdma_spi1_tx;
extern DMA_HandleTypeDef hdma_spi2_rx;
extern DMA_HandleTypeDef hdma_spi4_tx;
extern DMA_HandleTypeDef hdma_usart3_rx;
extern DMA_HandleTypeDef hdma_usart3_tx;

void SystemClock_Config(void);
void Board_PeripheralClock_Config(void);
void MX_GPIO_Init(void);
void MX_GPDMA1_Init(void);
void MX_I2C1_Init(void);
void MX_I2C3_Init(void);
void MX_SPI4_Init(void);
void MX_I2S1_Init(void);
void MX_I2S2_Init(void);
void MX_USART3_UART_Init(void);
void MX_SDMMC1_SD_Init(void);
void MX_TIM1_Init(void);
void MX_TIM2_Init(void);
void MX_IWDG_Init(void);

void Board_Init(void);

#ifdef __cplusplus
}
#endif

#endif /* KIKU_BOARD_H */

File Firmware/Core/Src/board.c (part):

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  __HAL_RCC_GPIOE_CLK_ENABLE();

  /* Safe power-on states: peripherals held reset/muted; LCD deselected. */
  HAL_GPIO_WritePin(GPIOE, LCD_DC_Pin | LCD_RST_Pin | TLV_RST_Pin | AMP_SD_MODE_Pin,
                    GPIO_PIN_RESET);
  HAL_GPIO_WritePin(GPIOE, LCD_CS_Pin, GPIO_PIN_SET);
  HAL_GPIO_WritePin(GPIOD, BM83_RST_Pin | BM83_MFB_Pin | SI4705_RST_Pin, GPIO_PIN_RESET);

  gpio.Pin = LCD_DC_Pin | LCD_CS_Pin | LCD_RST_Pin | TLV_RST_Pin | AMP_SD_MODE_Pin;
  gpio.Mode = GPIO_MODE_OUTPUT_PP;
  gpio.Pull = GPIO_NOPULL;
  gpio.Speed = GPIO_SPEED_FREQ_LOW;
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  gpio.Pin = BM83_RST_Pin | BM83_MFB_Pin | SI4705_RST_Pin;
  HAL_GPIO_Init(GPIOD, &gpio);

  gpio.Pin = PUSH_1_Pin | PUSH_2_Pin;
  gpio.Mode = GPIO_MODE_INPUT;
  gpio.Pull = GPIO_PULLUP;
  HAL_GPIO_Init(GPIOC, &gpio);
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  gpio.Pull = GPIO_PULLUP;
  HAL_GPIO_Init(GPIOA, &gpio);

  gpio.Pin = HP_DET_Pin;
  gpio.Mode = GPIO_MODE_INPUT;
  gpio.Pull = GPIO_NOPULL;
  HAL_GPIO_Init(GPIOD, &gpio);
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  HAL_GPIO_Init(GPIOD, &gpio);

  /* BQ25895 INT and MAX17048 ALRT already have external 10 kOhm pull-ups. */
  gpio.Pin = BQ_INT_Pin | MAX_INT_Pin;
  gpio.Mode = GPIO_MODE_IT_FALLING;
  gpio.Pull = GPIO_NOPULL;
  HAL_GPIO_Init(GPIOE, &gpio);
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  }

  /* Keep the native SPI1 data directions. PCB net names are codec-relative:
   * PA7/SPI1_MOSI -> /DIN -> TLV320 DIN and MAX98357 DIN (MCU transmit),
   * PA6/SPI1_MISO <- /DOUT <- TLV320 DOUT (codec ADC return). */
}

void MX_I2S2_Init(void)
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    Error_Handler();
  }

  /* BM83 DT1 is wired to PB14 / SPI2_MISO.  On STM32H523 the dedicated I2S
   * receive data path uses the opposite SPI data input unless IOSWP is set.
   * Without this swap RFS1/SCLK1 clock correctly and RX DMA runs, but RXDR is
   * filled with zeroes even though valid audio is present on PB14. */
  if (HAL_I2S_EnableIOSwap(&hi2s2) != HAL_OK)
  {
    Error_Handler();
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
